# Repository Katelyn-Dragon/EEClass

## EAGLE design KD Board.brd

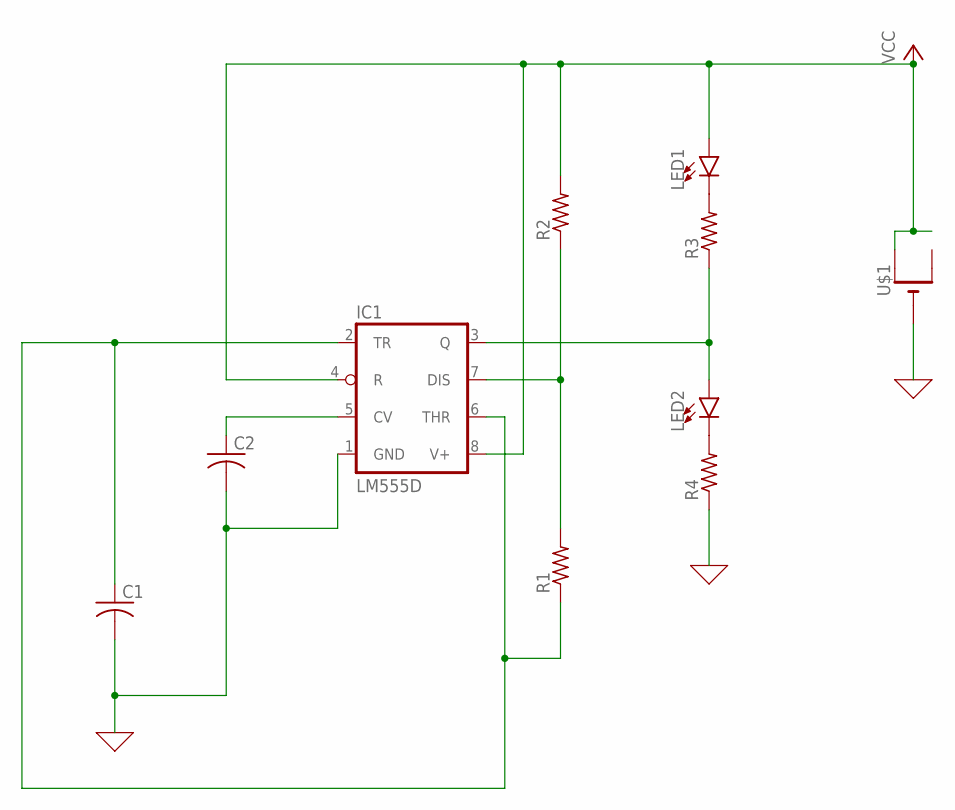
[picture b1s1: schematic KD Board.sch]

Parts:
C1, C2: C-USC0805K; C0805K
IC1: LM555D; SO08
LED1, LED2: LED; LED_5MM
R1, R2, R3, R4: R-US_M0805; M0805
U$1: CR1220THM; CR1220-THM

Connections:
0: C1.2, C2.2, IC1.1 (GND), R4.1, U$1.-
unnamed: C2.1, IC1.5 (CV)
unnamed: C1.1, IC1.2 (TR), IC1.6 (THR), R1.1
unnamed: IC1.7 (DIS), R1.2, R2.1
unnamed: LED1.K (C), R3.2
unnamed: LED2.K (C), R4.2
unnamed: IC1.3 (Q), LED2.A, R3.1
VCC: IC1.4 (R), IC1.8 (V+), LED1.A, R2.2, U$1.+1 (+)

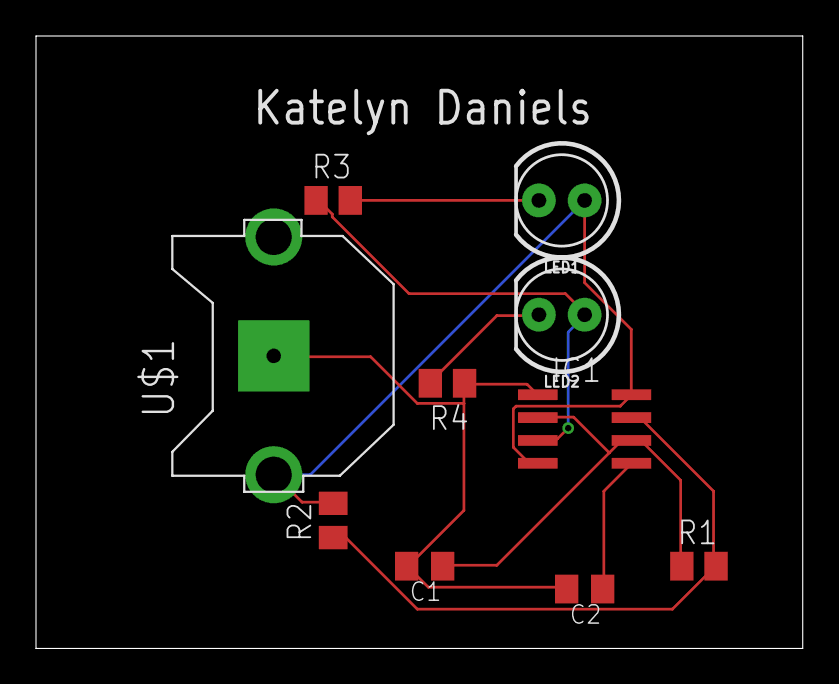
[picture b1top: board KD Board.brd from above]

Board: 2 copper layers, 42.6 x 34.0 mm, 10 parts (0 on the bottom side), 8 nets.

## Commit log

2018-05-08 Moved name to silk layer. Board not square. Minor fixes.
